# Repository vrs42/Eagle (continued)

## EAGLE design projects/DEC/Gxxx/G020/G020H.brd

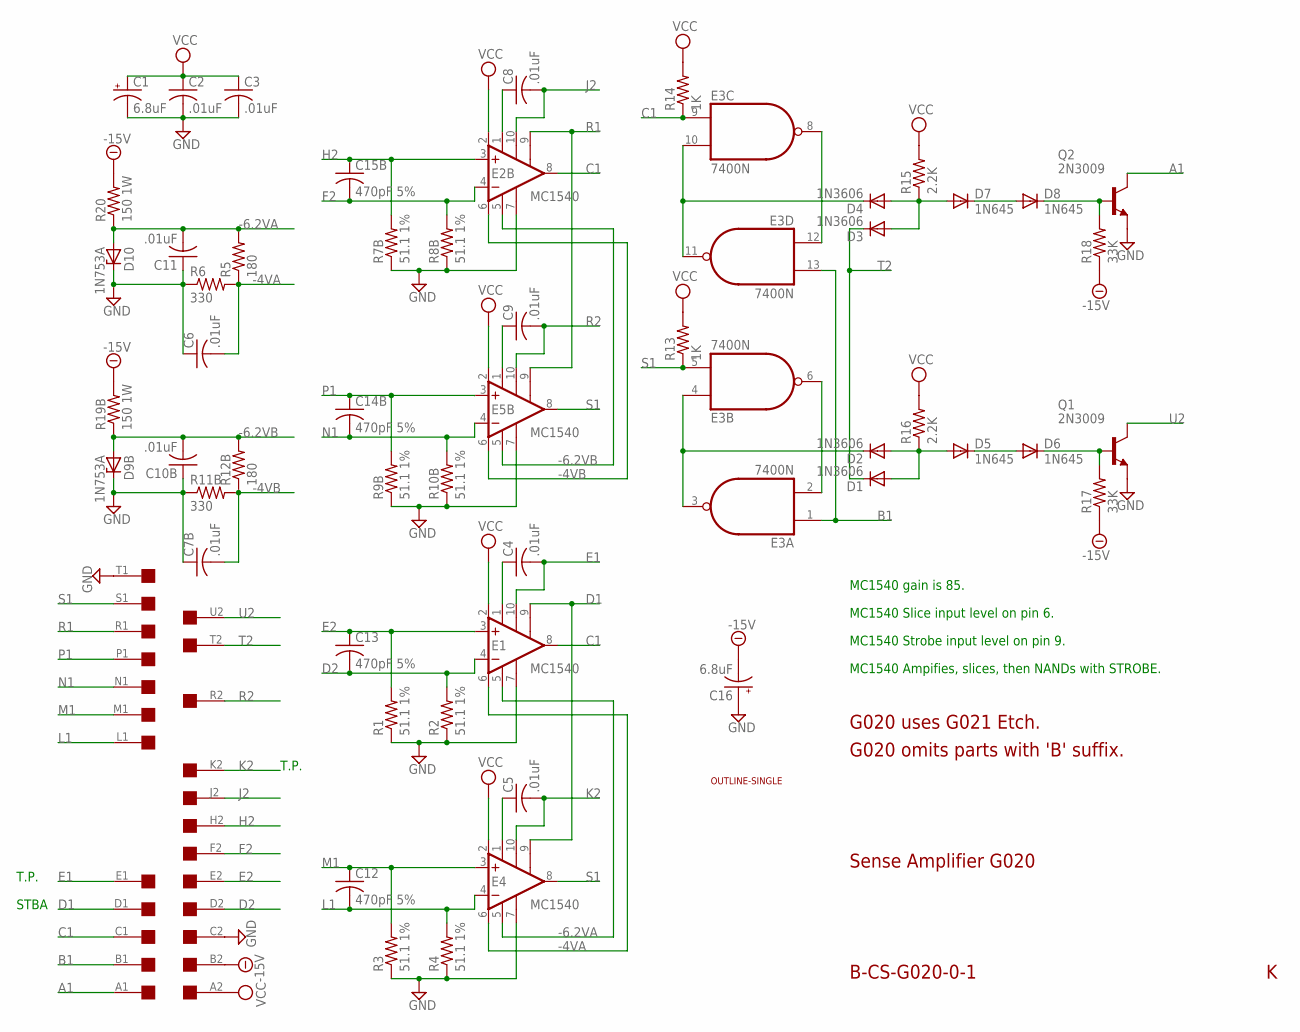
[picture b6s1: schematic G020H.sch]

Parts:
C1, C16: 6.8uF; E12-8
C2, C3, C4, C5, C6, C7B, C8, C9, C10B, C11: .01uF; C050-025X075
C12, C13, C14B, C15B: 470pF 5%; C050-025X075
D1, D2, D3, D4: 1N3606; DO35-10
D5, D6, D7, D8: 1N645; DO35-10
D9B, D10: 1N753A; DO35Z10
E1, E2B, E4, E5B: MC1540; 602B
E3: 7400N; DIL14
Q1, Q2: 2N3009; TO5
R1, R2, R3, R4, R7B, R8B, R9B, R10B: 51.1 1%; 0207/15
R5, R12B: 180; 0207/10
R6, R11B: 330; 0207/10
R13, R14: 1K; 0207/10
R15, R16: 2.2K; 0207/10
R17, R18: 33K; 0207/10
R19B, R20: 150 1W; 0414/20
U$1: SINGLE; EDGE-CON2
U$2: OUTLINE-SINGLE; SINGLE

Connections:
-4VA: C6.2, E1.6 (SLICE), E4.6 (SLICE), R5.1, R6.2
-4VB: C7B.2, E2B.6 (SLICE), E5B.6 (SLICE), R11B.2, R12B.1
-6.2VA: C11.2, D10.A, E1.5 (V-), E4.5 (V-), R5.2, R20.1
-6.2VB: C10B.2, D9B.A, E2B.5 (V-), E5B.5 (V-), R12B.2, R19B.1
-15V: C16.-, R17.1, R18.1, R19B.2, R20.2, U$1.B2
A1: Q2.3 (C), U$1.A1
B1: E3.1 (I0), E3.13 (I1), U$1.B1
C1: E1.8 (OUT), E2B.8 (OUT), E3.9 (I0), R14.1, U$1.C1
D1: E1.9 (ISTROBE), E4.9 (ISTROBE), U$1.D1
D2: C13.2, E1.4 (-IN), R2.2, U$1.D2
E1: C4.2, E1.10 (CEXTB), U$1.E1
E2: C13.1, E1.3 (+IN), R1.2, U$1.E2
F2: C15B.2, E2B.4 (-IN), R8B.2, U$1.F2
GND: C1.-, C2.2, C3.2, C6.1, C7B.1, C10B.1, C11.1, C16.+, D9B.C, D10.C, E1.7 (GND), E2B.7 (GND), E3.7 (GND), E4.7 (GND), E5B.7 (GND), Q1.1 (E), Q2.1 (E), R1.1, R2.1, R3.1, R4.1, R6.1, R7B.1, R8B.1, R9B.1, R10B.1, R11B.1, U$1.C2, U$1.T1
H2: C15B.1, E2B.3 (+IN), R7B.2, U$1.H2
J2: C8.2, E2B.10 (CEXTB), U$1.J2
K2: C5.2, E4.10 (CEXTB), U$1.K2
L1: C12.2, E4.4 (-IN), R4.2, U$1.L1
M1: C12.1, E4.3 (+IN), R3.2, U$1.M1
N1: C14B.2, E5B.4 (-IN), R10B.2, U$1.N1
unnamed: C4.1, E1.1 (CEXTA)
unnamed: C8.1, E2B.1 (CEXTA)
unnamed: C5.1, E4.1 (CEXTA)
unnamed: C9.1, E5B.1 (CEXTA)
unnamed: E3.8 (O), E3.12 (I0)
unnamed: D1.A, D2.A, D5.A, R16.1
unnamed: D4.C, E3.10 (I1), E3.11 (O)
unnamed: D2.C, E3.3 (O), E3.4 (I0)
unnamed: E3.2 (I1), E3.6 (O)
unnamed: D3.A, D4.A, D7.A, R15.1
unnamed: D7.C, D8.A
unnamed: D5.C, D6.A
unnamed: D8.C, Q2.2 (B), R18.2
unnamed: D6.C, Q1.2 (B), R17.2
P1: C14B.1, E5B.3 (+IN), R9B.2, U$1.P1
R1: E2B.9 (ISTROBE), E5B.9 (ISTROBE), U$1.R1
R2: C9.2, E5B.10 (CEXTB), U$1.R2
S1: E3.5 (I1), E4.8 (OUT), E5B.8 (OUT), R13.1, U$1.S1
T2: D1.C, D3.C, U$1.T2
U2: Q1.3 (C), U$1.U2
VCC: C1.+, C2.1, C3.1, E1.2 (V+), E2B.2 (V+), E3.14 (VCC), E4.2 (V+), E5B.2 (V+), R13.2, R14.2, R15.2, R16.2, U$1.A2

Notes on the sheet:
T.P.
STBA
MC1540 gain is 85.
MC1540 Slice input level on pin 6.
MC1540 Strobe input level on pin 9.
MC1540 Ampifies, slices, then NANDs with STROBE.
Sense Amplifier G020
B-CS-G020-0-1
G020 omits parts with 'B' suffix.
G020 uses G021 Etch.

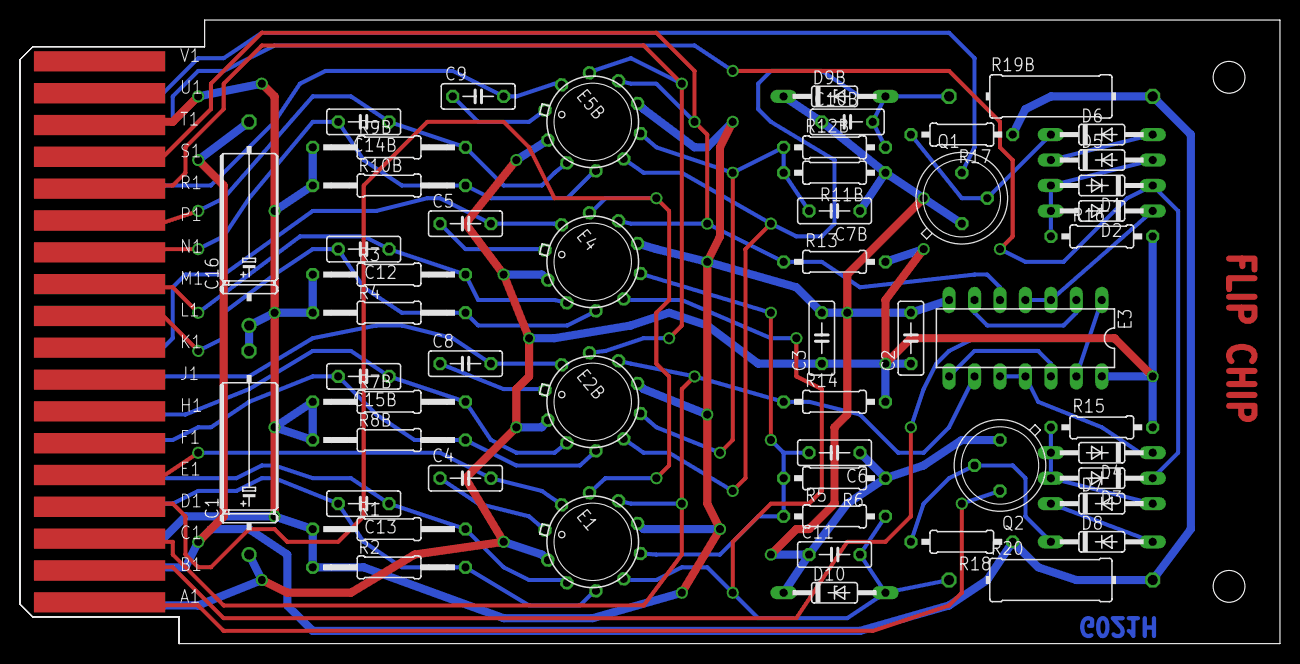
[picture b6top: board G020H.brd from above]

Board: 3 copper layers, 125.7 x 62.2 mm, 55 parts (0 on the bottom side), 41 nets.
